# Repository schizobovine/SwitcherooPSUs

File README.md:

SwitcherooPSUs
==============

Various switching power supplies I've "designed", mostly from reference diagrams and copious amounts of Magic Smoke.

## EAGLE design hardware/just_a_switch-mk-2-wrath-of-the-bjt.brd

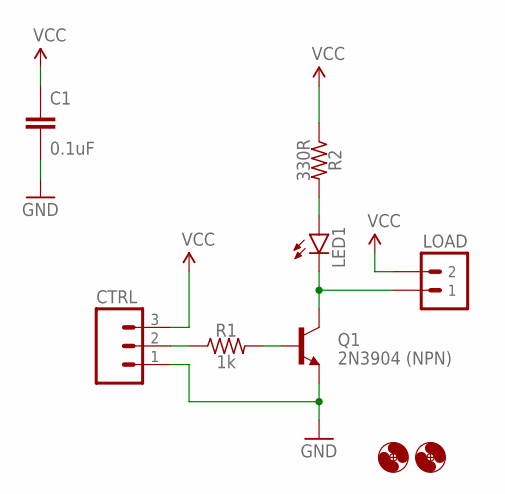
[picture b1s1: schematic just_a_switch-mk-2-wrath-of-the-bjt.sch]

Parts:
C1: 0.1uF; C025-024X044
CTRL: M03JST-PTH; JST-3-PH-RA-PTH
H1, H2: HOLE#2; HOLE-#2
LED1: LED3MM
LOAD: M02JST-PTH-RA-SMALLPADS; JST-2-PH-RA-PTH-SMALLPADS
Q1: 2N3904 (NPN); TO-92-AMMO
R1: 1k; RESISTOR-AXIAL-PTH-6.35MM
R2: 330R; RESISTOR-AXIAL-PTH-6.35MM

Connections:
GND: C1.2, CTRL.1, Q1.1 (E)
LOAD: LED1.K (C), LOAD.1, Q1.3 (C)
unnamed: CTRL.2, R1.P$1 (1)
unnamed: LED1.A, R2.P$2 (2)
unnamed: Q1.2 (B), R1.P$2 (2)
VCC: C1.1, CTRL.3, LOAD.2, R2.P$1 (1)

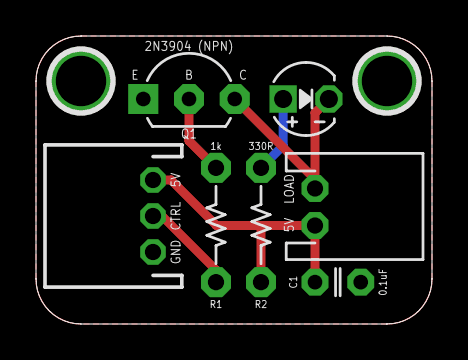
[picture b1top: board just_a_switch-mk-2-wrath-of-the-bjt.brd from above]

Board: 2 copper layers, 22.0 x 16.0 mm, 10 parts (1 on the bottom side), 6 nets.

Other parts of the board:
U$1: CC-BY-SA-4.0-NO-URL

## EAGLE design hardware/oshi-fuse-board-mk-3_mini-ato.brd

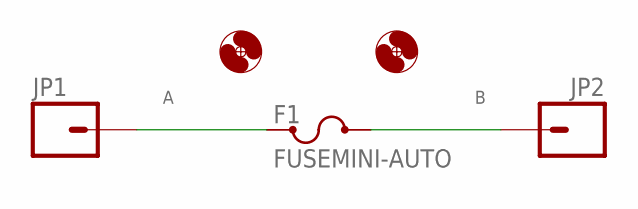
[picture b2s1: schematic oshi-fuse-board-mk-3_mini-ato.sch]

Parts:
F1: FUSEMINI-AUTO; KEYSTONE-MINI-AUTO-FUSE-HOLDER
H1, H2: HOLE#4; HOLE-#4
JP1, JP2: M01SCREWITGOOD; 1X01-RING-TERM-6-32-FAT

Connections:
A: F1.P1@1 (1), F1.P1@2 (1), JP1.P$1, JP1.P$2, JP1.P$3, JP1.P$4
B: F1.P2@1 (2), F1.P2@2 (2), JP2.P$1, JP2.P$2, JP2.P$3, JP2.P$4

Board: 2 copper layers, 5 parts (0 on the bottom side), 2 nets, no tracks yet.

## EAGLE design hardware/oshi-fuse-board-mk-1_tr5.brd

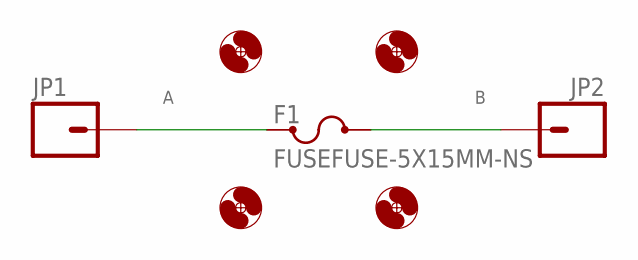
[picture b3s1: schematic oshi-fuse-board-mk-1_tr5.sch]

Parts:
F1: FUSEFUSE-5X15MM-NS; FUSE-2AG-NS
H1, H2, H3, H4: HOLE#2; HOLE-#2
JP1, JP2: M01SCREW-IT; 1X01-RING-TERM-6-32

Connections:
A: F1.1, F1.1@1 (1), JP1.P$1, JP1.P$2, JP1.P$3, JP1.P$4, JP1.P$5
B: F1.2, JP2.P$1, JP2.P$2, JP2.P$3, JP2.P$4, JP2.P$5

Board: 2 copper layers, 7 parts (0 on the bottom side), 2 nets, no tracks yet.

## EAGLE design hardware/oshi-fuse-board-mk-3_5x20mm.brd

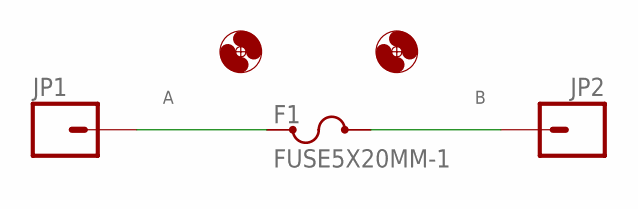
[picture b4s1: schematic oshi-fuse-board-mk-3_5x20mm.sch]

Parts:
F1: FUSE5X20MM-1; FUSE_5MM
H1, H2: HOLE#2; HOLE-#2
JP1, JP2: M01SCREWITGOOD; 1X01-RING-TERM-6-32-FAT

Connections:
A: F1.1, F1.2 (1), JP1.P$1, JP1.P$2, JP1.P$3, JP1.P$4
B: F1.3 (2), F1.4 (2), JP2.P$1, JP2.P$2, JP2.P$3, JP2.P$4

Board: 2 copper layers, 6 parts (2 on the bottom side), 2 nets, no tracks yet.

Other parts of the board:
U$1: COW_SMALL

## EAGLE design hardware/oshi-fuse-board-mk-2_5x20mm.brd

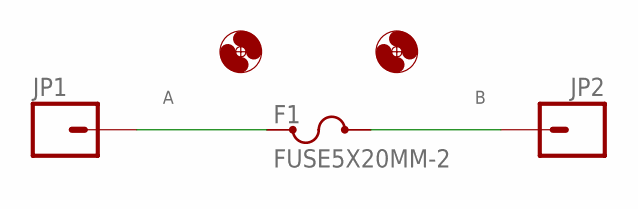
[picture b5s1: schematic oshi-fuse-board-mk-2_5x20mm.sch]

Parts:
F1: FUSE5X20MM-2; FUSE-2AG
H1, H2: HOLE#2; HOLE-#2
JP1, JP2: M01SCREWITGOOD; 1X01-RING-TERM-6-32-FAT

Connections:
A: F1.1, F1.1@1 (1), JP1.P$1, JP1.P$2, JP1.P$3, JP1.P$4
B: F1.2, F1.2@2 (2), JP2.P$1, JP2.P$2, JP2.P$3, JP2.P$4

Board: 2 copper layers, 6 parts (2 on the bottom side), 2 nets, no tracks yet.

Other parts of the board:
U$1: COW_SMALL

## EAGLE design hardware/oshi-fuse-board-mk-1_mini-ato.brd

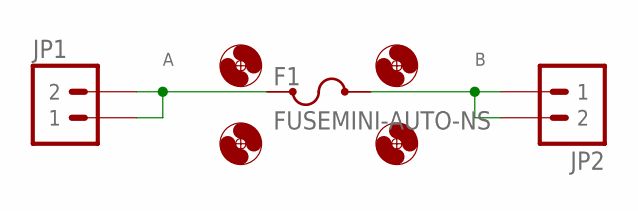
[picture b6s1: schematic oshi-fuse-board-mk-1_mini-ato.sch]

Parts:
F1: FUSEMINI-AUTO-NS; KEYSTONE-MINI-AUTO-FUSE-HOLDER-NS
H1, H2, H3, H4: HOLE#2; HOLE-#2
JP1, JP2: M023.5MM; SCREWTERMINAL-3.5MM-2

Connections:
A: F1.P1@1 (1), F1.P1@2 (1), JP1.1, JP1.2
B: F1.P2@1 (2), F1.P2@2 (2), JP2.1, JP2.2

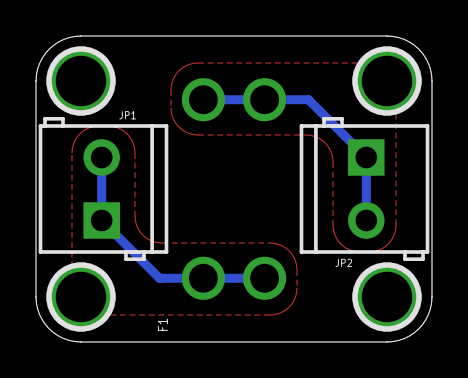
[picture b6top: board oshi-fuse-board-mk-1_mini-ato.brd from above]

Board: 2 copper layers, 22.0 x 17.0 mm, 8 parts (1 on the bottom side), 2 nets.

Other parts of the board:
U$1: COW_SMALL

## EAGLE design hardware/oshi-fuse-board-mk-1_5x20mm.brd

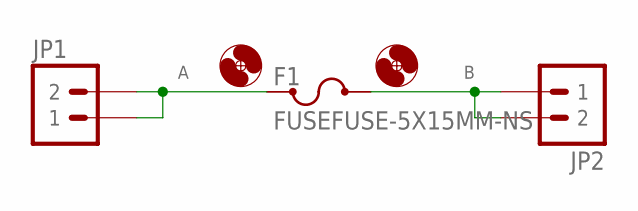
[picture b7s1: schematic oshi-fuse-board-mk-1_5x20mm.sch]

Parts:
F1: FUSEFUSE-5X15MM-NS; FUSE-2AG-NS
H1, H2: HOLE#2; HOLE-#2
JP1, JP2: M023.5MM; SCREWTERMINAL-3.5MM-2

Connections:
A: F1.1, F1.1@1 (1), JP1.1, JP1.2
B: F1.2, JP2.1, JP2.2

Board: 2 copper layers, 5 parts (0 on the bottom side), 2 nets, no tracks yet.

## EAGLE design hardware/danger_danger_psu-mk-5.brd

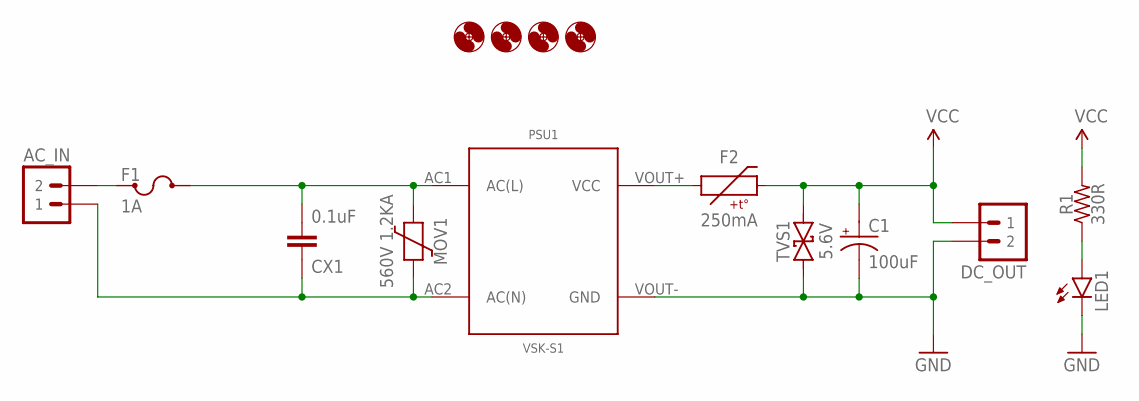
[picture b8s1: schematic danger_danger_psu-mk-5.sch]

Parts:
AC_IN: M023.5MM; SCREWTERMINAL-3.5MM-2
C1: 100uF; E2,5-6
CX1: 0.1uF; XC10B6
DC_OUT: M02JST-PTH-VERT; JST-2-PH-VERT-PTH
F1: 1A; KEYSTONE-MINI-AUTO-FUSE-HOLDER
F2: 250mA; PTC-PTH-5.08MM
H1, H2, H3, H4: HOLE#2; HOLE-#2
LED1: LED3MM
MOV1: 560V 1.2KA; VAR-5.08MM-PTH
PSU1: VSK-S1
R1: 330R; RESISTOR-AXIAL-PTH-5.08MM
TVS1: 5.6V; DO-41-TVS-BI-10.16MM

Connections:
GND: C1.-, DC_OUT.2, LED1.K (C), PSU1.VOUT- (GND), TVS1.P$2 (2)
unnamed: AC_IN.1, CX1.1, MOV1.2, PSU1.AC2 (AC(N))
unnamed: CX1.2, F1.P2@1 (2), F1.P2@2 (2), MOV1.1, PSU1.AC1 (AC(L))
unnamed: AC_IN.2, F1.P1@1 (1), F1.P1@2 (1)
unnamed: LED1.A, R1.P$1 (1)
unnamed: F2.P$1 (1), PSU1.VOUT+ (VCC)
VCC: C1.+, DC_OUT.1, F2.P$2 (2), R1.P$2 (2), TVS1.P$1 (1)

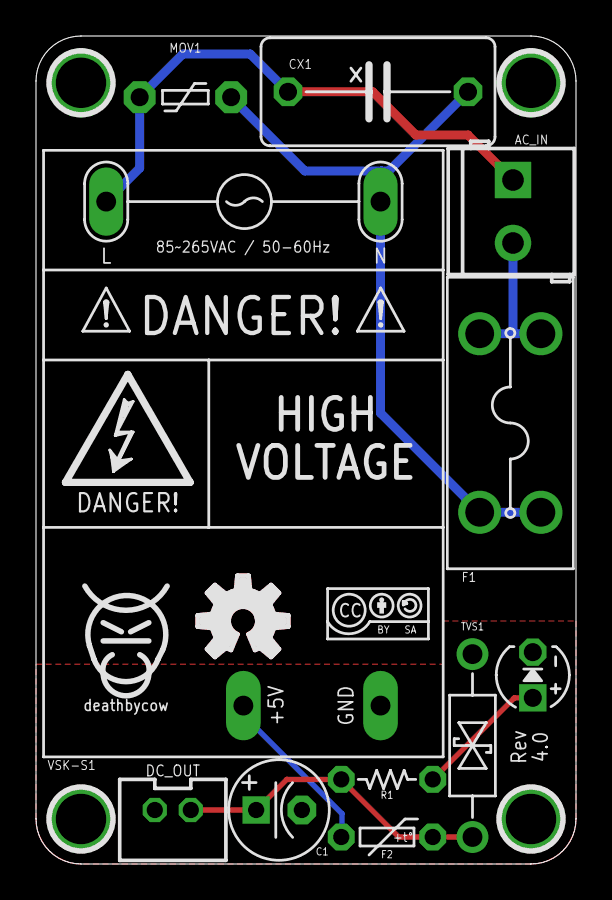
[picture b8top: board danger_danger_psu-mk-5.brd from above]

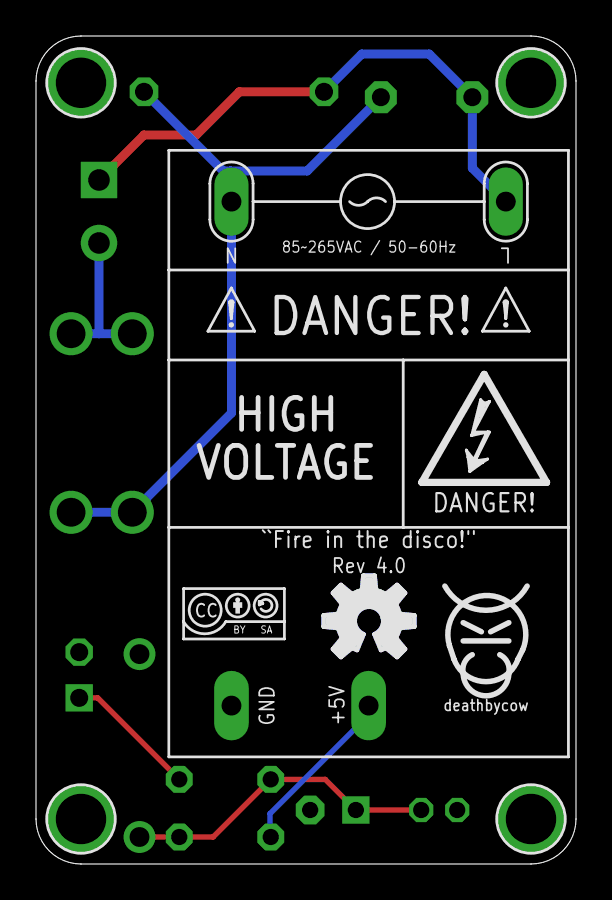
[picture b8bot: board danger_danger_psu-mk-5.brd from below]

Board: 2 copper layers, 30.0 x 46.0 mm, 21 parts (3 on the bottom side), 7 nets.

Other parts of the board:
U$1, U$6: COW_SMALL
U$3, U$7: CC-BY-SA-4.0-NO-URL
U$4, U$5: OSHWLOGO_BOT_0.2

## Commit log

2014-10-08 fixed a few mistakes, still rearranging
2014-10-08 redo
2014-10-09 a saner layout with a few fixes, but still not complete
2014-10-09 standardizedish ignore file for both C and Eagle files
2014-10-15 blah
2014-10-27 renaming to something more descriptive
2014-11-13 attempting to build an AC power supply; we'll see how this goes
2014-11-14 more designfail
2015-01-09 PSU to use for various things; pricier but at least known places to mount crap. should make a smaller verision if such a thing is possible w/o being super power wasteful.
2015-01-09 older version that sucks
2015-01-09 and nuke it from orbit now
2015-01-09 simple but multipurpose N-MOSFET breakout
2015-01-11 added tap for post-fuse and MOV/CX protected 120AC to accomodate devices that need a pass through as well. traces widened to 1mm to accomodate increased power possible (hopefully that's enough for 10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
2015-01-17 Stupid simple N-MOSFET breakout with LED for debugging
2015-01-29 mark 4 of the generic psu board, not fully laid out yet.
2015-01-29 mark 5 psu, removed a few components and fully laid out
2015-01-29 simple fuse breakout pcb
2015-01-29 another fuse breakout, this time for mini-ato fuses instead of 5x20 cartridge fuses
2015-01-31 finished layout for the miniato version
2015-01-31 new mini ATO version with ring terminals instead of screw terminals. confusingly, ring terminals also have screws.
2015-01-31 new 5x20mm cartridge version with ring terminals instead of screw terminals. confusingly, ring terminals also have screws
2015-01-31 new 5x20mm cartridge version for reasons
2015-01-31 horridly misnamed but i will fix later
2015-01-31 removing because
2015-01-31 yet another one
2015-02-07 BJT sounds like a sex act
